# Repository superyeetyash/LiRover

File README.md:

# LiRover, Curated by Alex, Anish, Om, Yash

## Overview

Welcome to LiRover! This hardware for Hackclub's Stardance event will be centered around a hardware initiative by 4 high schoolers.

After a failed rocket idea, we settled on an RC car with a LiDAR sensor attached that can create a comprehensive map of its surroundings. This is done from scratch by creating a 3D printed chassis, custom PCB, and an embedded control system. This project is controlled through a Raspberry Pi Zero 2 W and a Raspberry Pi Pico W. The robot will combine LiDAR sensing, an IMU (which includes an accelerometer for linear acceleration, gyroscope for measuring angular rotation, and magnetometer for magnetic field and acting as a compass), motor drivers, and wheel odometry to estimate its position and generate a real-time 2D "minimap" of its surrounding area. To control it, we implemented a Bluetooth module for SLAM development (Simultaneous Localization and Mapping, essentially enabling the robot to construct a map and track its position).

---

## Features

- Custom CAD and 3D-printed chassis for the RC car
- Custom PCB with onboard power regulation, fusing, and dedicated LiDAR/motor connectors
- Bluetooth remote control
- Real time LiDAR mapping
- IMU-based tracking
    - Accelerometer for linear acceleration
    - 3-plane gyroscope for angular rotation
    - Magnetometer for magnetic field detection

---

## Hardware

### Computing
- Raspberry Pi Zero 2 W
- Raspberry Pi Pico W

### Sensors
- 2D/3D Lidar
- IMU
- Wheel Encoders (??)

### Electronics
- Custom PCB (Pico W + Pi Zero 2 W header, LiDAR connector, screw terminals for motor/battery)
- Motor driver
- Lithium Battery Pack
- Voltage regulation circuitry
- Bluetooth module
- Onboard fuse protection

### Mechanical
- Fully custom 3D-printed chassis
- Custom motor mounts
- 3D-printed power switch housing

---

## Software

### Raspberry Pi Zero 2 W
- Sensor fusion
- Mapping
- Localization
- Bluetooth comms
- Dashboard server
- Robot logic / Robot comms

### Raspberry Pi Pico W (*Communicates with the Raspberry Pi Zero 2 W*)
- Sensor reading
- Motor Pulse Width Modulation (PWM)
- Encoder Feedback

---

## Project Goals

- Design and develop a complete robotics platform
- Develop an embedded control system
- Generate a live 2D map using LiDAR and motion estimation (Main goal!!!)

---

<picture>
  
</picture>

<picture>
 
</picture>

---

## Parts List

PARTS LIST IS IN BOM.csv

---

## Repository Structure

_Coming Soon!!_

---

## Devlog

Check out [JOURNAL.md](./JOURNAL.md) for build progress and updates.

---

## License

This project is licensed with the MIT License.

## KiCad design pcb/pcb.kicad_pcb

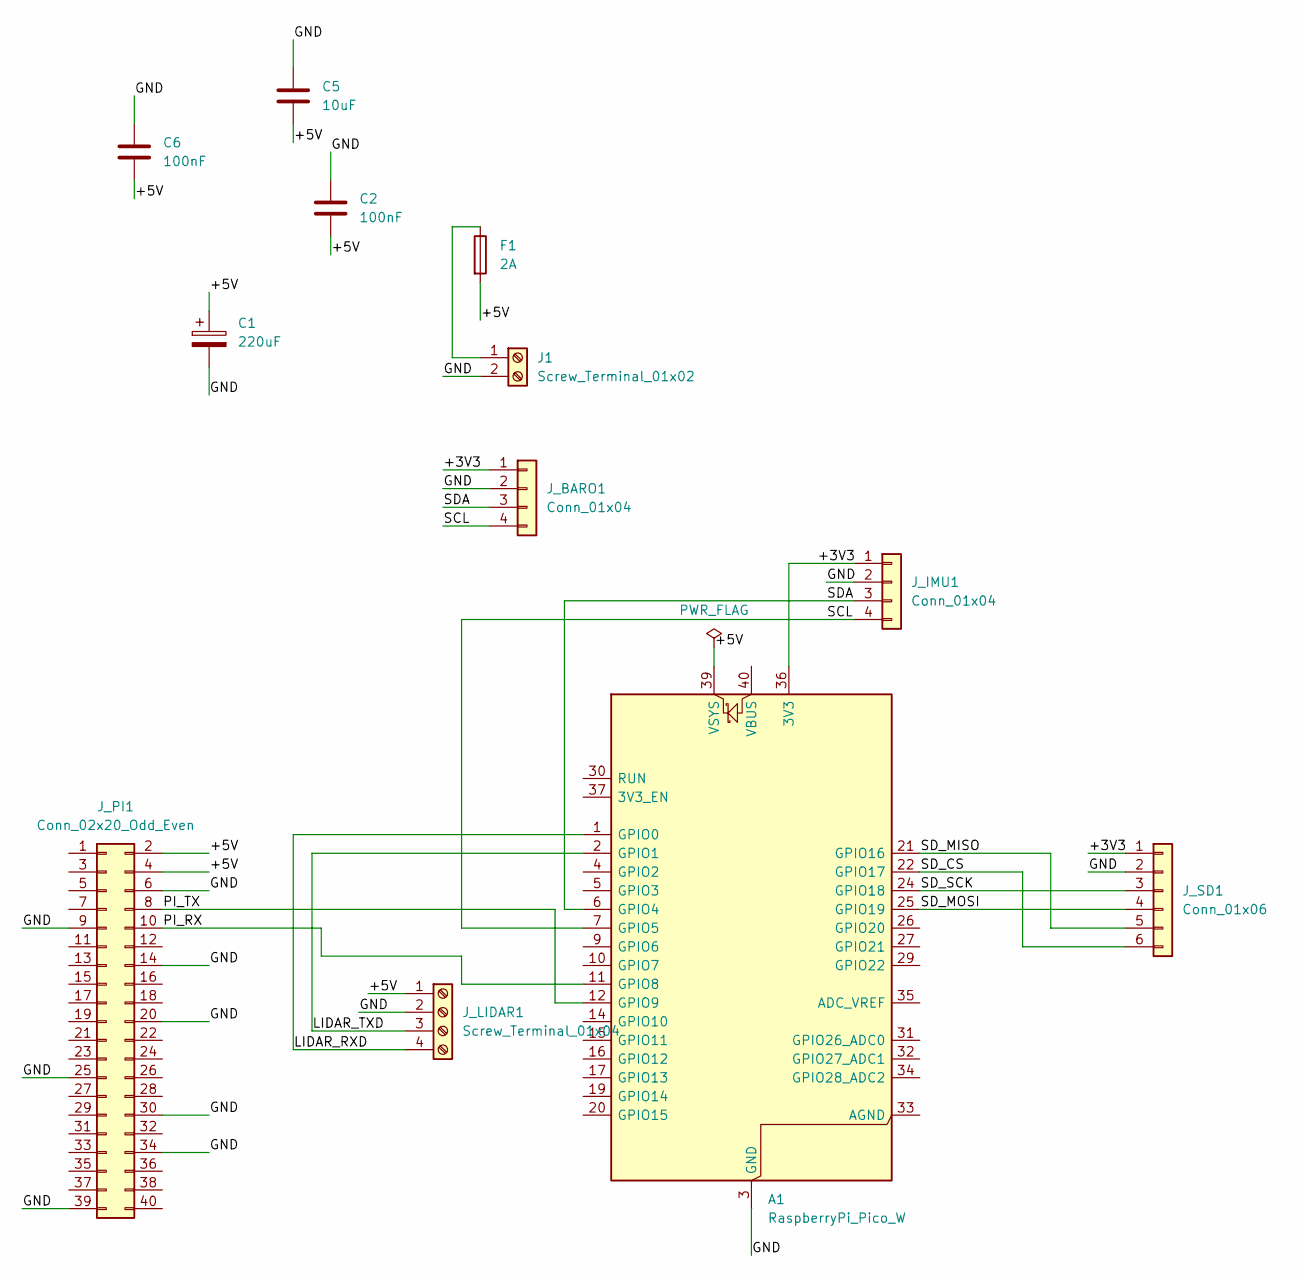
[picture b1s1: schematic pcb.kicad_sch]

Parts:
A1: RaspberryPi_Pico_W; RaspberryPi_Pico_W_SMD_HandSolder
C1: 220uF; CP_Radial_D6.3mm_P2.50mm
C2, C6: 100nF; C_Disc_D7.5mm_W5.0mm_P5.00mm
C5: 10uF; CP_Radial_D6.3mm_P2.50mm
F1: 2A; Fuse_1206_3216Metric
J1: Screw_Terminal_01x02; PinHeader_1x02_P2.54mm_Vertical
J_BARO1: Conn_01x04; PinSocket_1x04_P2.54mm_Vertical
J_IMU1: Conn_01x04; PinSocket_1x04_P2.54mm_Vertical
J_LIDAR1: Screw_Terminal_01x04; PinHeader_1x04_P2.54mm_Vertical
J_PI1: Conn_02x20_Odd_Even; PinSocket_2x20_P2.54mm_Vertical
J_SD1: Conn_01x06; PinSocket_1x06_P2.54mm_Vertical

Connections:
/+3V3: A1.36 (3V3), J_BARO1.1, J_IMU1.1, J_SD1.1
/+5V: A1.39 (VSYS), C1.1, C2.2, C5.2, C6.2, F1.2, J_LIDAR1.1, J_PI1.2, J_PI1.4
/GND: A1.3 (GND), A1.8 (GND), A1.13 (GND), A1.18 (GND), A1.23 (GND), A1.28 (GND), A1.38 (GND), C1.2, C2.1, C5.1, C6.1, J1.2, J_BARO1.2, J_IMU1.2, J_LIDAR1.2, J_PI1.6, J_PI1.9, J_PI1.14, J_PI1.20, J_PI1.25, J_PI1.30, J_PI1.34, J_PI1.39, J_SD1.2
/LIDAR_RXD: A1.1 (GPIO0), J_LIDAR1.4
/LIDAR_TXD: A1.2 (GPIO1), J_LIDAR1.3
/PI_RX: A1.11 (GPIO8), J_PI1.10
/PI_TX: A1.12 (GPIO9), J_PI1.8
/SCL: A1.7 (GPIO5), J_BARO1.4, J_IMU1.4
/SDA: A1.6 (GPIO4), J_BARO1.3, J_IMU1.3
/SD_CS: A1.22 (GPIO17), J_SD1.6
/SD_MISO: A1.21 (GPIO16), J_SD1.5
/SD_MOSI: A1.25 (GPIO19), J_SD1.4
/SD_SCK: A1.24 (GPIO18), J_SD1.3
unnamed: F1.1, J1.1

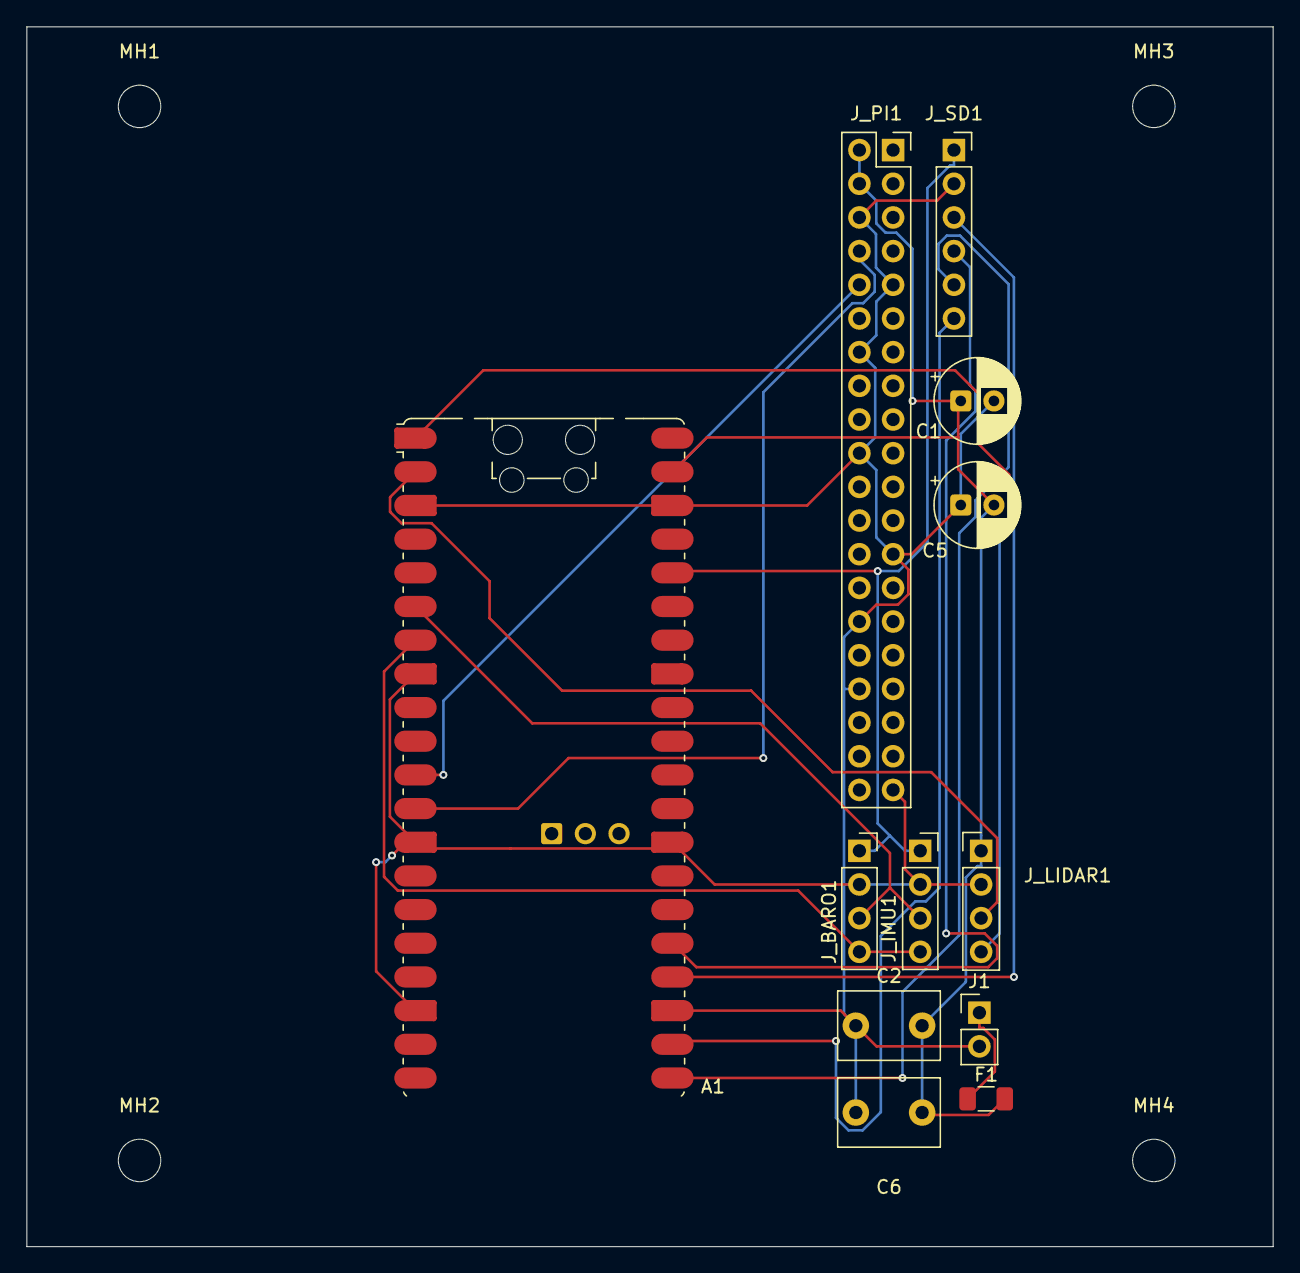
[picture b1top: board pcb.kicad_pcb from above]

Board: 2 copper layers, 94.0 x 92.0 mm, 16 parts (0 on the bottom side), 14 nets.

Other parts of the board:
MH1, MH2, MH3, MH4: MountingHole_3.2mm_M3

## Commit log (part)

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2026-06-20 Created README
2026-06-20 fixed readme plan and updated legal requirements
2026-06-29 README Creation With Project Details
2026-06-29 Remove empty StarPost folder
2026-06-29 Update README.md with project overview, features, hardware, software details, project goals, and repository structure
2026-06-29 Initialize project structure
